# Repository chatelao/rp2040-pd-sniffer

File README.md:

# RP2040 USB-PD Sniffer and Sink

This project provides two firmwares for a Raspberry Pi Pico or any other RP2040-based board to interact with the USB Power Delivery (USB-PD) protocol.

1.  **Sniffer:** A passive USB-PD sniffer that listens to the communication on a USB-C CC (Configuration Channel) line, decodes the messages in real-time, and prints them to the USB serial console.
2.  **Sink:** An active device that can negotiate a specific power profile from a USB-PD power adapter. This example is configured to request a 15V / 3A profile.

## Features

*   **Shared USB-PD Library:** All the common logic for decoding and encoding USB-PD messages is contained in a shared library.
*   **PIO-Based Sampling and Transmission:** Uses the RP2040's Programmable I/O (PIO) for both an 8x oversampled receiver (sniffer and sink) and a BMC transmitter (sink).
*   **Real-Time Decoding:** Performs full, real-time decoding of the physical layer protocol.
*   **Self-Contained Build:** The project is configured with a modern CMake build system and includes the Raspberry Pi Pico SDK as a submodule.
*   **Automated Builds:** A GitHub Actions workflow automatically builds both firmware targets on every push to the `main` branch.

## Building the Firmware

This project uses CMake and requires the ARM GCC toolchain.

### Prerequisites

*   `git`
*   `cmake`
*   `gcc-arm-none-eabi`

On a Debian-based system (like Ubuntu), you can install these with:
```bash
sudo apt-get update
sudo apt-get install -y git cmake gcc-arm-none-eabi
```

### Build Steps

1.  **Clone the repository:**
    ```bash
    git clone https://github.com/your-username/rp2040-pd-sniffer.git
    cd rp2040-pd-sniffer
    ```

2.  **Initialize the Submodules:**
    ```bash
    git submodule update --init --recursive
    ```

3.  **Run the Build:**
    ```bash
    cmake -B build -S .
    cmake --build build --parallel
    ```

4.  **Find the Firmware:**
    If the build is successful, you will find the flashable `.uf2` files inside the `build` directory:
    *   `build/sniffer.uf2`
    *   `build/sink.uf2`

## Flashing and Usage

### Sniffer

1.  **Flash the Firmware:** Flash `sniffer.uf2` to your Pico.
2.  **Monitor the Output:** Open a serial monitor and connect to the Pico's virtual COM port. You will see the decoded USB-PD messages.

### Sink

1.  **Flash the Firmware:** Flash `sink.uf2` to your Pico.
2.  **Connect to Power Adapter:** Connect the CC line of your circuit to a USB-PD power adapter.
3.  **Monitor the Output:** Open a serial monitor. The application will print a message if it finds and requests the 15V/3A profile.

## Documentation

The documentation for this project is available [here](https://chatelao.github.io/rp2040-pd-sniffer/).

## Acknowledgements

The development of the flexible, data-driven sink implementation was significantly influenced by the work of Manuel Bleichenbacher on the [usb-pd-arduino](https://github.com/manuelbl/usb-pd-arduino) project. His project served as an invaluable reference for understanding the USB-PD protocol and implementing a robust state machine.

The `usb-pd-arduino` project is licensed under the MIT License, and its license is included below:

```
MIT License

Copyright (c) 2023 Manuel Bleichenbacher

Permission is hereby granted, free of charge, to any person obtaining a copy
of this software and associated documentation files (the "Software"), to deal
in the Software without restriction, including without limitation the rights
to use, copy, modify, merge, publish, distribute, sublicense, and/or sell
copies of the Software, and to permit persons to whom the Software is
furnished to do so, subject to the following conditions:

The above copyright notice and this permission notice shall be included in all
copies or substantial portions of the Software.

THE SOFTWARE IS PROVIDED "AS IS", WITHOUT WARRANTY OF ANY KIND, EXPRESS OR
IMPLIED, INCLUDING BUT NOT LIMITED TO THE WARRANTIES OF MERCHANTABILITY,
FITNESS FOR A PARTICULAR PURPOSE AND NONINFRINGEMENT. IN NO EVENT SHALL THE
AUTHORS OR COPYRIGHT HOLDERS BE LIABLE FOR ANY CLAIM, DAMAGES OR OTHER
LIABILITY, WHETHER IN AN ACTION OF CONTRACT, TORT OR OTHERWISE, ARISING FROM,
OUT OF OR IN CONNECTION WITH THE SOFTWARE OR THE USE OR OTHER DEALINGS IN THE
SOFTWARE.
```

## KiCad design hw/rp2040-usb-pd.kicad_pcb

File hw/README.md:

A minimal HW frontend for the USB-PD control

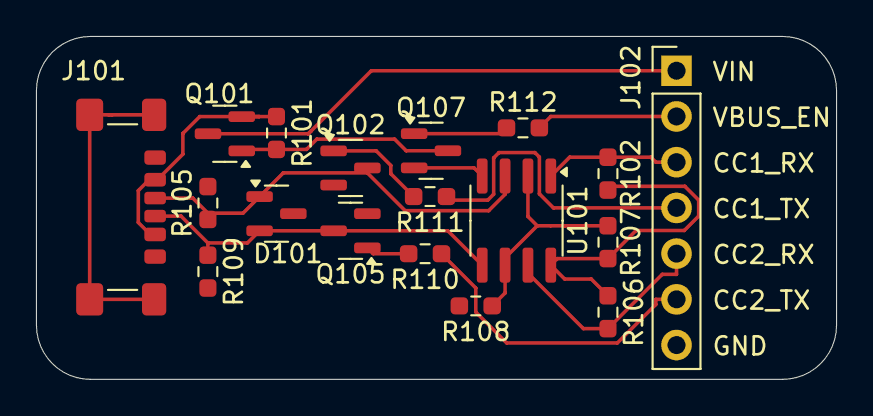
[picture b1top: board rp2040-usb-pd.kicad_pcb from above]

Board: 4 copper layers, 44.4 x 19.0 mm, 18 parts (0 on the bottom side), 16 nets.

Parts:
D101: SP0502BAHT; SOT-23
J101: USB_C_Receptacle_USB2.0_14P; USB_C_Receptacle_GCT_USB4135-GF-A_6P_TopMnt_Horizontal
J102: Conn_01x07; PinHeader_1x07_P2.54mm_Vertical
Q101: MMBT3906; SOT-23
Q102, Q105, Q107: MMBT3904; SOT-23
R101, R102, R106, R108, R110, R111, R112: 10k; R_0603_1608Metric_Pad0.98x0.95mm_HandSolder
R105, R109: 5k1; R_0603_1608Metric_Pad0.98x0.95mm_HandSolder
R107: 120k; R_0603_1608Metric_Pad0.98x0.95mm_HandSolder
U101: LM393; SOIC-8_3.9x4.9mm_P1.27mm

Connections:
+3V3: R102.1, R106.1, R107.1, U101.8 (V+)
/275mV: R107.2, R108.1, U101.2 (-), U101.6 (-)
/RP2040_CC1_RX: J102.3, R102.2, U101.1
/RP2040_CC1_TX: J102.4, R111.1
/RP2040_CC2_RX: J102.5, R106.2, U101.7
/RP2040_CC2_TX: J102.6, R110.1
/RP2040_VBUS_EN: J102.2, R112.2
/USB_CC1: D101.1 (K), J101.A5 (CC1), Q102.3 (C), R105.1, U101.3 (+)
/USB_CC2: D101.2 (K), J101.B5 (CC2), Q105.3 (C), R109.1, U101.5 (+)
/VBUS: J101.A9 (VBUS), J101.B9 (VBUS), Q101.2 (E), R101.1
/VIN: J102.1, Q101.3 (C)
GND: D101.3 (A), J101.A12 (GND), J101.B12 (GND), J102.7, Q102.2 (E), Q105.2 (E), Q107.2 (E), R105.2, R108.2, R109.2, U101.4 (V-)
unnamed: Q101.1 (B), Q107.3 (C), R101.2
unnamed: Q102.1 (B), R111.2
unnamed: Q105.1 (B), R110.2
unnamed: Q107.1 (B), R112.1

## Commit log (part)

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2025-10-18 Add GitHub Actions workflow for building firmware
2025-10-18 Add README for minimal HW frontend
2025-10-18 Implement USB-PD sniffer with PIO and DMA
2025-10-18 Format clock rate definitions for readability
2025-10-18 I have added the necessary enums, structs, and defines to src/main.c for managing the decoder's state, storing the 4b/5b lookup table, and representing decoded packets.
    I have implemented the BMC decoder function `bmc_decoder_feed` and added a forward declaration for the next stage of the decoding process.
    I have implemented the 4b/5b and packet decoder state machine in the `process_decoded_bit` function.
    I have integrated the decoder into the main loop by replacing the `printf` in `sniffer_loop` with a call to the new decoding functions and added the packet printing logic.
2025-10-18 Add '4b5b' branch to workflow triggers
2025-10-18 feat: Implement USB-PD message decoder
    Adds the necessary logic to decode USB Power Delivery (USB-PD) messages from the raw data captured by the RP2040 sniffer.
    The implementation includes:
    - A Biphase Mark Code (BMC) decoder to translate the oversampled signal into a clean bitstream.
    - A 4b/5b symbol decoder to convert 5-bit symbols into 4-bit nibbles.
    - A packet decoder state machine to reconstruct the USB-PD packet structure, including header, data objects, and CRC.
    - Integration of the decoder into the main loop to process data from the DMA buffer and print decoded packets to the console.
2025-10-19 Fix: Correct GitHub Actions build workflow
    This commit fixes the continuous integration build process defined in the GitHub Actions workflow file.
    The key changes are:
    - Updated the `actions/checkout@v4` step to correctly and automatically initialize git submodules by setting `submodules: 'true'`.
    - Removed the fragile manual `git clone` step for the Pico SDK, as the checkout action now handles it.
    - Modernized and simplified the CMake configuration and build steps, using `cmake -B build` and `cmake --build build --parallel` for a more robust and standard process.
    - Corrected the path in the `upload-artifact` step to ensure the compiled firmware (`.uf2` file) is correctly saved.
2025-10-19 feat(ci): Automatically create release with UF2 artifact
    This commit updates the GitHub Actions workflow to automatically create a new GitHub Release for every successful build on the `main` branch.
    The key changes are:
    - Replaced the `actions/upload-artifact` step with the `softprops/action-gh-release` action.
    - Configured the new step to create a pre-release tagged with the build's commit SHA.
    - The compiled `rp2040_pd_sniffer.uf2` file is now attached directly to the release, allowing for easy, direct download without needing to unzip an artifact.
    - This only triggers on pushes to the `main` branch to avoid creating releases for pull requests.
2025-10-19 feat: Add 15V/3A sink application and refactor into shared library
    This commit introduces a major restructuring of the project to support multiple firmware targets and improve code reuse.
    Key changes include:
    1. **Project Restructuring:**
    * The source code is now organized into a shared library (`src/pd_library`) and two separate applications (`src/sniffer` and `src/sink`).
    * The `CMakeLists.txt` file has been rewritten to build the library and generate two distinct firmware files: `sniffer.uf2` and `sink.uf2`.
    2. **New Sink Application:**
2025-10-20 feat: Add unit tests, HIL tests, and restructure project
    This commit introduces a major restructuring of the project to support multiple firmware targets, a native unit test suite, and hardware-in-the-loop (HIL) tests.
    - **Project Structure:** The codebase is now organized into a shared `pd_library`, two main applications (`sniffer` and `sink`), and a `test_firmware` directory for HIL tests.
    - **Unit Testing:** A native unit test suite using the Unity framework has been added. The build system is configured with a `NATIVE_BUILD` option to compile and run these tests on a host machine.
    - **Hardware-in-the-Loop (HIL) Testing:** New firmware for HIL testing has been added. This includes a "pin
2025-10-21 feat: Implement complete USB-PD message decoding and sink logic
    This change implements a full pipeline for decoding and acting on USB Power Delivery (USB-PD) messages.
    Key features and changes:
    - Implemented a robust BMC and 4b/5b decoder state machine for reliable packet decoding.
    - Corrected the CRC-32 implementation to match the USB-PD specification.
    - Implemented a sink protocol state machine capable of negotiating a 15V/3A power profile.
    - Restructured the project into a shared library (`pd_library`) and two separate applications (`sniffer` and `sink`).
2025-10-22 feat: Add USB-PD source mode with proprietary VDM support
    This commit introduces a new USB Power Delivery (PD) source mode to the firmware. This mode is designed to support a proprietary charging protocol, in anticipation of the Nintendo Switch 2, by unlock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
    Key changes include:
    - A new `pd_source` library with a state machine to manage the source logic.
    - A new `source` application that utilizes the `pd_source` library.
    - A native unit test to verify the VDM unlock mechanism.
    - Updates to the build system to integrate the new components.
2025-10-22 feat: Add Hardware Abstraction Layer and STM32 support
    This commit introduces a Hardware Abstraction Layer (HAL) to enable multi-platform support. The initial focus is on the existing RP2040 (Pico) and the new STM32 platform.
    Key changes:
    - Created a HAL with a generic interface for GPIO, DMA, and CRC.
    - Refactored the Pico implementation to use the new HAL.
    - Added a stub implementation for the STM32 HAL.
    - Updated the build system to allow target selection.
2025-10-22 fix: Resolve cppcheck errors and WIP on failing tests
    This commit addresses the following issues:
    - Resolves cppcheck missingInclude errors by updating include paths.
    - Fixes a cppcheck badBitmaskCheck warning.
    - Keeps unused functions that are part of the public API.
    This commit also includes several work-in-progress attempts to fix the failing CRC32 and encoding tests. These tests are still not passing, and the changes are being submitted to save the current sta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
2025-10-22 feat: Add VDM injection and pass-through to MITM
    This change refactors the "man-in-the-middle" (MITM) application to support injecting Vendor Defined Messages (VDMs).
    The MITM application now terminates the USB-PD protocol on both ports, allowing it to correctly manage the protocol state for each connection. This resolves a critical bug where MessageIDs were not b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
    A new helper function, pd_build_vdm_header, has been added to the pd_library to facilitate the creation of VDM packets. The MITM application uses this function to inject a VDM after a 15V power contr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
    The pd_sink module has been refactored to be instance-based, allowing multiple sink inst
2025-10-23 This commit resolves the failing CI/CD pipeline by correctly configuring the `cppcheck` static analysis.
    The GitHub Actions workflow has been updated to:
    1. Install necessary dependencies (cmake, gcc-arm-none-eabi).
    2. Initialize the `pico-sdk` submodule.
    3. Run CMake to generate a `compile_commands.json` file.
    4. Execute `cppcheck` using the generated compilation database, which resolves the `missingInclude` errors.
    Additionally, this commit includes the following fixes:
2025-10-23 docs: Add license investigation for usb-pd-arduino
    This commit adds a new documentation file, docs/license_investigation.md, which summarizes the findings of an investigation into the usb-pd-arduino project. The investigation confirmed that the proje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
2025-10-23 feat: Implement CRC32 and flexible PD sink
    This commit introduces several improvements to the USB-PD library.
    - Implements a correct, table-driven CRC32 function to replace the previous placeholder.
    - Adds new unit tests to verify the CRC32 implementation.
    - Refactors the `pd_sink` state machine to be flexible, allowing it to parse source capabilities and request specific power profiles.
    - Updates the `mitm` application to demonstrate the new sink functionality by requesting a 15V, 3A power profile.
2025-10-23 fix(pd_sink): Correct PDO selection logic
    The PDO selection logic in `pd_sink.c` did not correctly choose the most optimal power profile when multiple suitable options were available at the same voltage. It would select the first suitable pr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
    This commit corrects the logic to ensure that when multiple suitable PDOs are available at the same voltage, the one with the lowest current that still meets the requirement is chosen.
    A new test case has been added to verify this specific scenario. The test fails before this fix and passes after, ensuring the bug is resolved and preventing regressions. The `pd_transmit_packet` func
2025-10-24 Refactor: Introduce HAL and PHY Layers
    This commit introduces a significant refactoring of the codebase to improve modularity, portability, and overall code quality.
    The key changes are:
    - A Hardware Abstraction Layer (HAL) has been introduced to encapsulate hardware-specific logic for the Raspberry Pi Pico.
    - The physical layer (PHY) has been refactored into a separate module with a stateful, stream-based decoder.
    - The `sink` and `sniffer` applications have been updated to use the new HAL, simplifying their main application logic.
    - The `pd_sink` module has been updated to be instance-based, allowing for multiple sink instances to run concurrently.
2025-10-24 fix: Trigger GitHub Actions on all branches
    This commit updates the GitHub Actions workflow to trigger on all branches for both push and pull_request events. This ensures that CI/CD runs on all branches, not just main.
2025-10-24 fix: Ignore submodules in cppcheck
    This commit updates the GitHub Actions workflow to ignore the pico-sdk and test/Unity submodules during the cppcheck static analysis. This prevents errors from being reported in third-party code.
2025-10-24 feat: Comprehensive refactor and CI fix
    This commit introduces a major architectural refactoring to improve modularity and portability. It also fixes the CI build, adds Doxygen documentation, and integrates it into the CI/CD pipeline.
    ### Refactoring
    - **Hardware Abstraction Layer (HAL):** A new HAL has been introduced to abstract all hardware-specific code (PIO, DMA, GPIO). This provides a clean, port-based API for applications.
    - **Physical Layer (PHY):** The low-level BMC and 5b/4b packet decoding logic has been extracted into a dedicated PHY layer, improving separation of concerns.
    - **Application Updates:** The `sink` and `sniffer` applications have been updated to use the new HAL, res
2025-10-24 fix(ci): Correct cppcheck ignore syntax
    This commit updates the GitHub Actions workflow to use the correct syntax for ignoring directories in `cppcheck`. The paths to be ignored must end with a trailing slash. This change will ensure that 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
2025-10-24 fix(ci): Filter compile_commands.json to fix cppcheck
    This commit updates the GitHub Actions workflow to filter the `compile_commands.json` file before running `cppcheck`. This is necessary because `cppcheck`'s `--project` option analyzes all files in t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
    The workflow now:
    1. Installs `jq`.
    2. Filters `compile_commands.json` to include only files from the `src` directory.
    3. Runs `cppcheck` on the new filtered `compile_commands_filtered.json` file.
    This ensures that `cppcheck` only analyzes the project's own source code, resolving the persistent build failures.
2025-10-24 debug(ci): Inspect compile_commands.json
    This commit temporarily modifies the GitHub Actions workflow to print the contents of the `compile_commands.json` file to the build log. This is a debugging step to understand the file paths generate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
